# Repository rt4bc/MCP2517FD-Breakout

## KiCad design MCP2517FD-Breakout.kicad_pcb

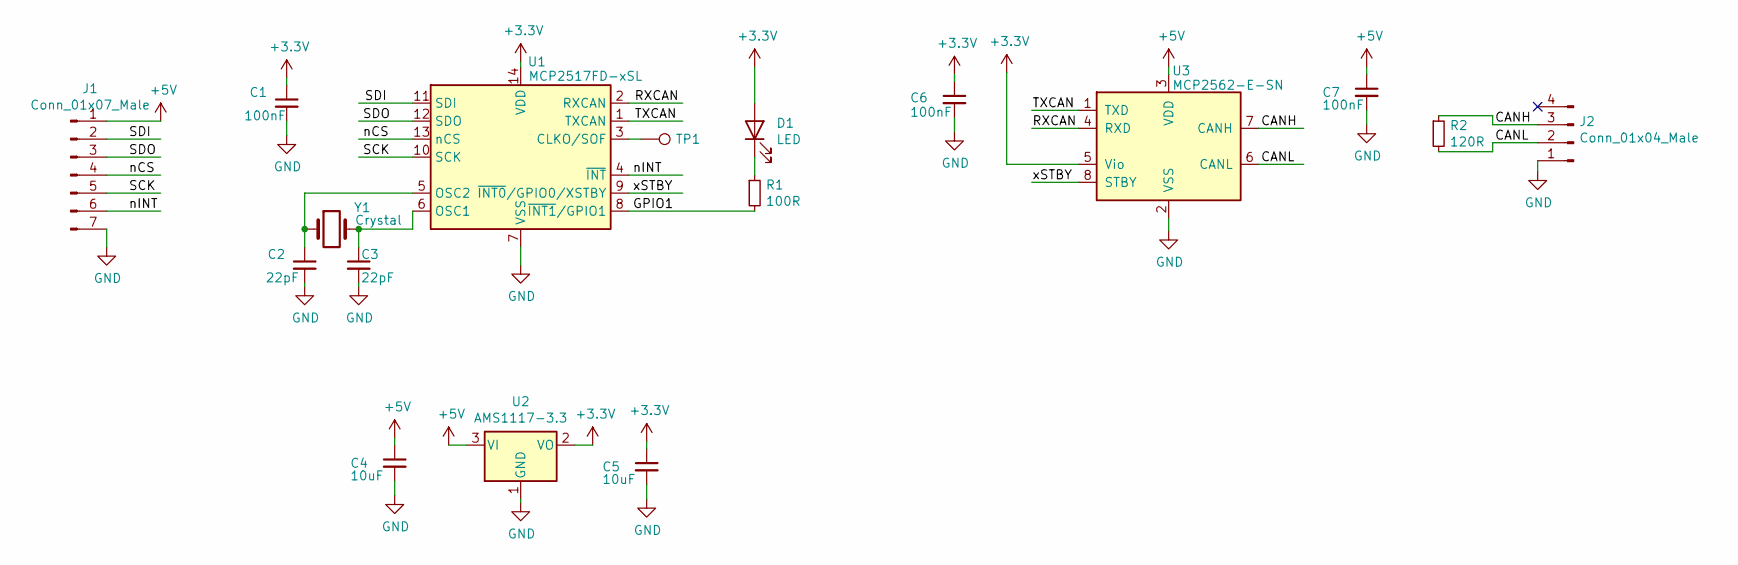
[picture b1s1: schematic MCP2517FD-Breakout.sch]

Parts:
C1, C6, C7: 100nF; C_0603_1608Metric_Pad1.08x0.95mm_HandSolder
C2, C3: 22pF; C_0603_1608Metric_Pad1.08x0.95mm_HandSolder
C4, C5: 10uF; C_0603_1608Metric_Pad1.08x0.95mm_HandSolder
D1: LED; LED_0603_1608Metric_Pad1.05x0.95mm_HandSolder
J1: Conn_01x07_Male; PinHeader_1x07_P2.54mm_Vertical
J2: Conn_01x04_Male; PinHeader_1x04_P2.54mm_Vertical
R1: 100R; R_0603_1608Metric_Pad0.98x0.95mm_HandSolder
R2: 120R; R_0603_1608Metric_Pad0.98x0.95mm_HandSolder
TP1: TestPoint; TestPoint_Pad_1.0x1.0mm
U1: MCP2517FD-xSL; SOIC-14_3.9x8.7mm_P1.27mm
U2: AMS1117-3.3; SOT-223-3_TabPin2
U3: MCP2562-E-SN; SOIC-8_3.9x4.9mm_P1.27mm
Y1: Crystal; Crystal_HC49-U_Vertical

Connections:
+3V3: C1.1, C5.1, C6.1, D1.2 (A), U1.14 (VDD), U2.2 (VO), U3.5 (Vio)
+5V: C4.1, C7.1, J1.1, U2.3 (VI), U3.3 (VDD)
/CANH: J2.3, R2.1, U3.7 (CANH)
/CANL: J2.2, R2.2, U3.6 (CANL)
/GPIO1: R1.2, U1.8 (~INT1~/GPIO1)
/RXCAN: U1.2 (RXCAN), U3.4 (RXD)
/SCK: J1.5, U1.10 (SCK)
/SDI: J1.2, U1.11 (SDI)
/SDO: J1.3, U1.12 (SDO)
/TXCAN: U1.1 (TXCAN), U3.1 (TXD)
/nCS: J1.4, U1.13 (nCS)
/nINT: J1.6, U1.4 (~INT)
/xSTBY: U1.9 (~INT0~/GPIO0/XSTBY), U3.8 (STBY)
GND: C1.2, C2.2, C3.2, C4.2, C5.2, C6.2, C7.2, J1.7, J2.1, U1.7 (VSS), U2.1 (GND), U3.2 (VSS)
unnamed: C2.1, U1.5 (OSC2), Y1.1
unnamed: C3.1, U1.6 (OSC1), Y1.2
unnamed: D1.1 (K), R1.1
unnamed: TP1.1, U1.3 (CLKO/SOF)

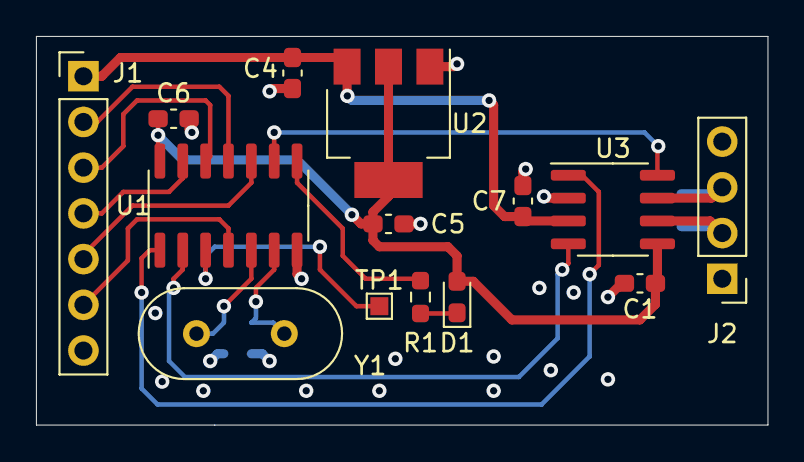
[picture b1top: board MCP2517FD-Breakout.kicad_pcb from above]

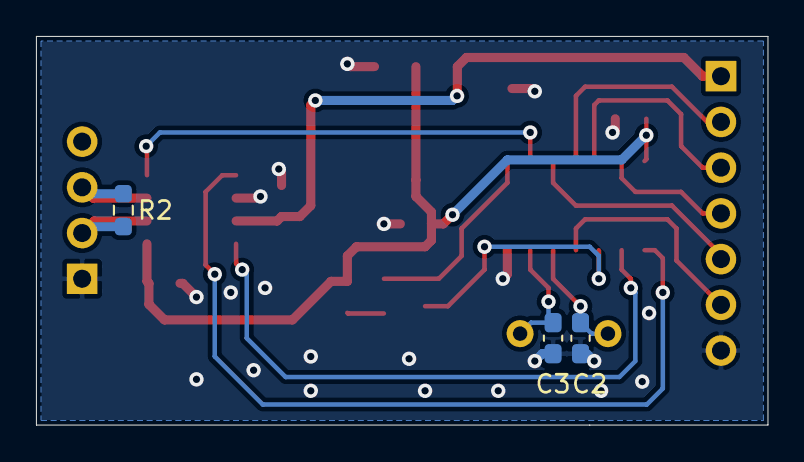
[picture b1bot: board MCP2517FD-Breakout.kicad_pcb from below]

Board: 2 copper layers, 40.6 x 21.6 mm, 17 parts (3 on the bottom side), 18 nets.

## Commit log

2021-01-01 update pcb, optime can tx rx routing
2021-01-08 solder picture
